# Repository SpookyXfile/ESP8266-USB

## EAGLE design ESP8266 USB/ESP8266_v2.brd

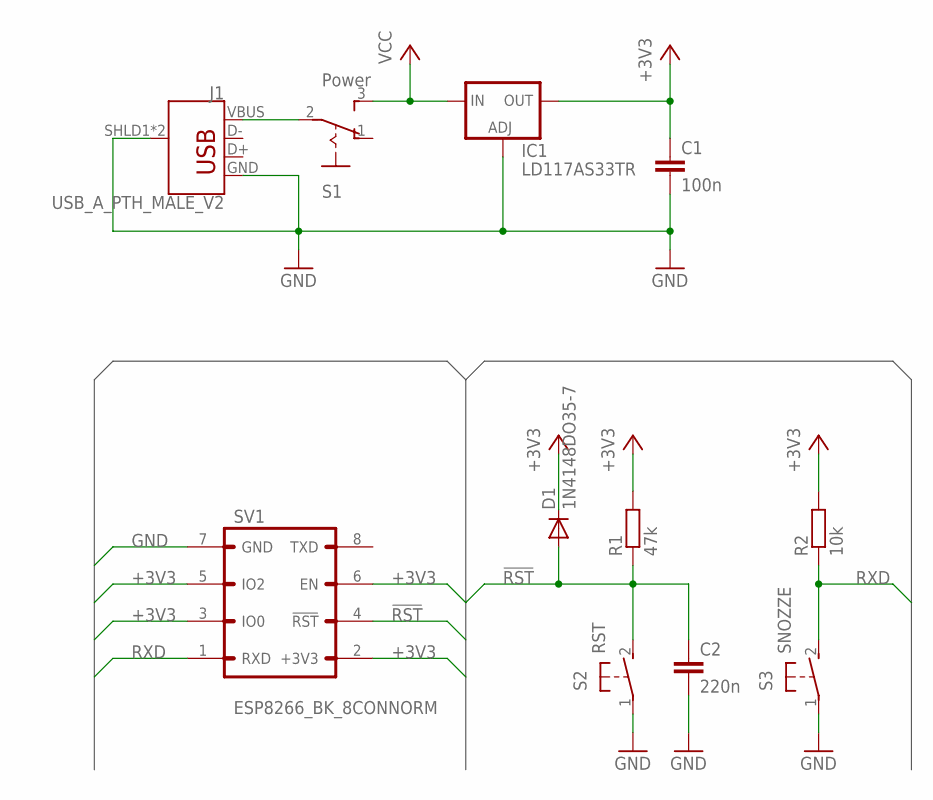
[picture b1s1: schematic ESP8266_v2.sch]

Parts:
C1: 100n; C050-025X075
C2: 220n; C050-025X075
D1: 1N4148DO35-7; DO35-7
IC1: LD117AS33TR; SOT223
J1: USB_A_PTH_MALE_V2; USB-A-H-V2
R1: 47k; 0204/5
R2: 10k; 0204/5
S1: Power; 255SB-B
S2: RST; DT6-1
S3: SNOZZE; DT6-1
SV1: ESP8266_BK_8CONNORM; ESP8266_8CON

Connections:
!RST: C2.1, D1.A, R1.1, S2.2 (S), SV1.4 (!RST)
+3V3: C1.1, D1.C, IC1.2 (OUT), IC1.4 (OUT), R1.2, R2.2, SV1.2 (+3V3), SV1.3 (IO0), SV1.5 (IO2), SV1.6 (EN)
GND: C1.2, C2.2, IC1.1 (ADJ), J1.GND, J1.SHLD1 (SHIELD), J1.SHLD2 (SHIELD), S2.1, S3.1, SV1.7 (GND)
unnamed: J1.VBUS, S1.2
RXD: R2.1, S3.2 (S), SV1.1 (RXD)
VCC: IC1.3 (IN), S1.3 (S)

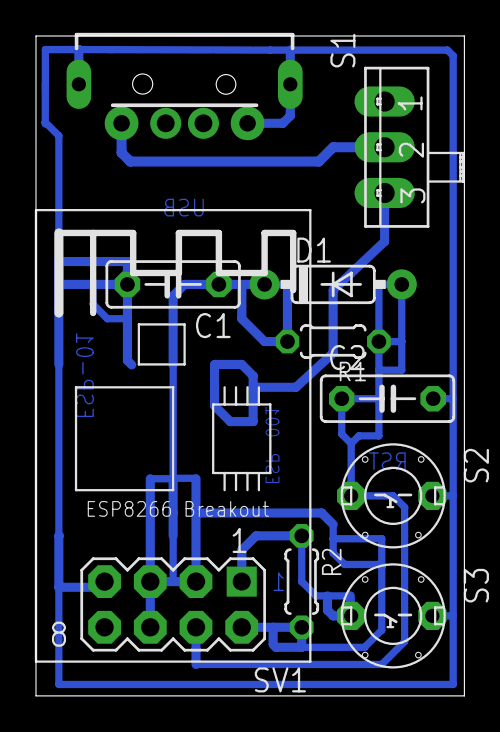
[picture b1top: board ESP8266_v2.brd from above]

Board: 2 copper layers, 23.8 x 36.7 mm, 11 parts (1 on the bottom side), 6 nets.
